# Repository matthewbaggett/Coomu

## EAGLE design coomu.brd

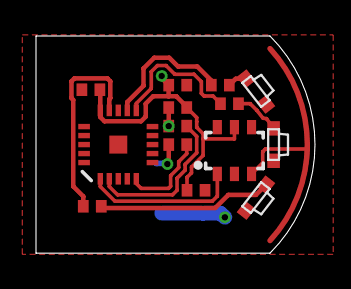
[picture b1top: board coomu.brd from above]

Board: 2 copper layers, 15.5 x 12.1 mm, 15 parts (1 on the bottom side), 13 nets.

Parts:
LEDS:BLUE: LED-SIDEFIRE0603; LED-0603-SIDEFIRE
LEDS:GREEN: LED-SIDEFIRE0603; LED-0603-SIDEFIRE
LEDS:R1: 150Ω; RESISTOR_0402
LEDS:R2, LEDS:R3: 100Ω; RESISTOR_0402
LEDS:RED: LED-SIDEFIRE0603; LED-0603-SIDEFIRE
MCU:C1: 100nF; CAPACITOR_0402
MCU:C2: 4.7uF; CAPACITOR_0402
MCU:R1, MCU:R2: 100Ω; RESISTOR_0402
MCU:R3: 1.5KΩ; RESISTOR_0402
MCU:U$1: ATTINY85; QFN20
TOUCH:C1: 100nF; CAPACITOR_0402
TOUCH:U$1: TTP223; SOT23-6
USB:U$1: USB

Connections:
5V: MCU:C1.1, MCU:C2.1, MCU:R3.1, MCU:U$1.15, TOUCH:C1.1, TOUCH:U$1.5, USB:U$1.VCC
BLUE: LEDS:R3.1, MCU:U$1.12
GND: LEDS:BLUE.P$1, LEDS:GREEN.P$1, LEDS:RED.P$1, MCU:C1.2, MCU:C2.2, MCU:U$1.8, TOUCH:C1.2, TOUCH:U$1.2, TOUCH:U$1.4, TOUCH:U$1.6, USB:U$1.GND
GREEN: LEDS:R2.1, MCU:U$1.11
LEDS:N$1: LEDS:R1.2, LEDS:RED.P$2
LEDS:N$2: LEDS:GREEN.P$2, LEDS:R2.2
LEDS:N$3: LEDS:BLUE.P$2, LEDS:R3.2
MCU:PB3: MCU:R2.2, MCU:U$1.2
MCU:PB4: MCU:R1.2, MCU:U$1.5
Q: MCU:U$1.1, TOUCH:U$1.1
RED: LEDS:R1.1, MCU:U$1.14
USB_D+: MCU:R1.1, USB:U$1.D+
USB_D-: MCU:R2.1, MCU:R3.2, USB:U$1.D-

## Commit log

2020-11-22 Initial
2020-11-22 Bob pointed out that LEDs that fire sideways exist. So much simpler.
2020-11-22 Made it shorter so it fits snugger in a port
